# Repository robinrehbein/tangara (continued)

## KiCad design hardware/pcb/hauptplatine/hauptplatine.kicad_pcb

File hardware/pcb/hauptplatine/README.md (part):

# Hauptplatine Endgerät (Nano-Player), Rev. 3b

> **STATUS Rev. 3b (2026-10-05): Review-Korrekturen eingearbeitet, neu exportiert, ERC 0 / DRC 0 (Abgleich gegen den Schaltplan), 0 offene Verbindungen – trotzdem NICHT bestellbar:** Blocker **B4** (ESP32-S31-WROOM-1 nicht lieferbar, 21 Wochen) ist offen, ein **Opus-Zweitreview der geänderten Schaltung/Platine ist Pflicht**, und die „Offenen Punkte“ unten (u. a. H2 VDDPST_SD, H3-Rest, H5-Impedanz, H6 Molex-Footprint, H10 USB4510/1,0 mm) sind nicht erledigt. Die Fertigungsdateien in `fertigung/` sind **Entwürfe**, keine Bestelldateien.
> - Platine **41 × 97 × 1,0 mm, 4 Lagen** (F.Cu / In1 GND-Fläche / In2 Signale + GND-Fläche / B.Cu), Ecken r = 4, Gerät ca. 44 × 100 × bis 10 mm; Plattenumriss, Ausschnitte, Löcher und hohe Teile **unverändert** gegenüber Rev. 3; **für das CAD neu**: Display-Stecker J20 (Molex, Körper x ±8,35 statt ±10,6, 1,0 mm statt 2,0 mm hoch) und zwei Rückseiten-Taster SW2/SW3 (Rückwand-Löcher), siehe Tabelle „Mechanik und Übergabe an das CAD“. Antenne des WROOM-1 liegt **innerhalb** der Kante (Keepout 18,6 × 7,6 mm, alle vier Kupferlagen, Regelbereich `antenna_keepout_board`). Lagenaufbau-Referenz (PCBWay 1,0 mm, aussen/innen 1 oz, Prepreg 7628 0,1855 mm, Kern 0,43 mm) ist in der Platinendatei hinterlegt, **von PCBWay für diese Bestellung nicht bestätigt**.
> - **DRC (kicad-cli, mit Abgleich gegen den Schaltplan): 0 Verstöße, 0 unverbundene Pads, 0 Footprint-Hinweise.** ERC: 0 Meldungen. Regeln: Bahn/Abstand 0,127 mm, Via 0,45/0,2 mm, **Kupfer–Kante 0,3 mm** (PCBWay-Standard; nur die Pads von Klinke/USB-C/microSD dürfen per eigener Regel in `hauptplatine.kicad_dru` bis 0,2 mm an den Randausschnitt), Loch–Loch 0,3 mm. Abgeschaltet und begründet: `silk_over_copper`, `silk_overlap`, `silk_edge_clearance` (PCBWay schneidet Siebdruck über Pads/Kante automatisch ab), `nonmirrored_text_on_back_layer`. Referenzbezeichner sind absichtlich **nicht** im Siebdruck (PCBWay arbeitet nach CPL).
> - **Was Rev. 3b gegenüber Rev. 3 ändert (Review `docs/REVIEW-HAUPTPLATINE.md`, Abschnitt 7):** B1 PCA9306 VREF2 = EN (ein 200 k, 100 pF); B2 R57 nicht bestückt; B3 Lader SEL = GND, PROG2 fest 500 mA, R39 2,7 k (ca. 370 mA); H1 Reset-Sicherung Q21/Q22/R250 (RESET bleibt ohne 3V3 low); H3 Leistungsnetze verbreitert (VBAT und VBUS jetzt fast durchgehend ≥ 0,4 mm, SYS_POWER zu 59 %, V5_HOST zu 59 %, VBUS_SW zu 66 %, 3V3-Zuleitung und BOOST_SW nur stellenweise bzw. weiter schmal); H4 J20 = Molex 503480-30 (1,0 mm) statt Hirose FH12 (2,0 mm); H5 USB-HS-Paar ca. 72 mm gekoppelt auf F.Cu; H7 R1 DNP-Option; H8 BOOT-/EN-Taster SW2/SW3 auf der Rückseite.
> - **Wie die Änderungen entstanden (ehrlich):** Der Ausgangsstand (Rev. 3, Router Freerouting 1.9.0 plus Handnacharbeit, siehe „Neuaufbau“) wurde **nicht neu geroutet**, sondern mit einem eigenen Raster-A*-Router (`tools/rt.py`, `tools/rev3b_stage*.py`, Ablauf `tools/rev3b_make.sh`) gezielt geändert: betroffene Pads umgenetzt, Bahnen entfernt/neu gezogen, USB-Paar neu verlegt (dabei wurde ein 3V3-Abschnitt auf andere Lagen verlegt). Alles ist per DRC mit exakter Abstandsprüfung geprüft, aber **nicht** von Hand nachgeprüft; Vorschaubilder ansehen.
> - **Nicht geprüft / Risiken:** keine Hardware, keine Simulation. USB-HS: Paar gekoppelt, **Impedanz nicht bestätigt** (Aufbau- und Breitenwahl bei PCBWay, Abschnitt „USB-HS“); Analogführung (HPREFA/B, Ladungspumpe) vom Router; Footprint des **Molex 503480** (J21, J20): Nagelpads geschätzt, **Form und Y-Lage ungeprüft**; Pegel der neuen Reset-Sicherung (2N7002T Vgs(th) nur aus dem Gedächtnis); CPL-Drehungen nicht gegen PCBWay geprüft; LCSC-Nummern größtenteils nicht verifiziert (Spalte „Nummer geprueft“).
> - Die Gerber-ZIP heißt nur dann ohne „NICHT_BESTELLEN“, wenn `tools/export.py` einen sauberen DRC sieht (hier der Fall); das heißt **nicht**, dass sie bestellbar ist.

Grundlage: `docs/AUDIO.md` (Audio-Kette), `TEILE.md` (Chipliste, Ziel-Maße). KiCad 9, Schaltplan und Platine werden aus Python-Skripten erzeugt (`tools/`). Rev. 2 (37 × 86 × 0,8) ist ersetzt, weil dort die Fläche nicht reichte und das Routing scheiterte.

## Inhalt des Ordners

| Pfad | Inhalt |
|---|---|
| `hauptplatine.kicad_pro`, `.kicad_sch`, `.kicad_pcb` | KiCad-Projekt (Schaltplan A1, eine Seite) |
| `lib/` | eigene Symbole (`Hauptplatine.kicad_sym`) und Footprints (`Hauptplatine.pretty`: ESP32-S31-WROOM-1 selbst erzeugt, Klinke und USB-C aus Tangara, X2QFN, Akkupads, Befestigungsloch) |
| `fertigung/hauptplatine_gerber_bohrdaten.zip` | Gerber (4 Lagen, 1,0 mm, Maske, Paste, Silkscreen, Kontur) und Bohrdaten (Excellon, PTH/NPTH getrennt) |
| `fertigung/hauptplatine_BOM_PCBWay.csv` | Stückliste im PCBWay-Format (Designator, Menge, Hersteller, MPN, Beschreibung, Gehäuseform, LCSC/Digi-Key nur wo geprüft; DNP markiert) |
| `fertigung/hauptplatine_CPL_PCBWay.csv` | Bestückungsdatei Oberseite und Unterseite (Designator, Mid X/Y, Layer, Rotation), ohne DNP-Teile |
| `fertigung/hauptplatine_schaltplan.pdf` | Schaltplan als PDF |
| `vorschau/` | SVG/PNG der Ober- und Unterseite |
| `pruefung/erc.rpt`, `pruefung/drc.rpt` | Berichte von `kicad-cli` |
| `quellen/` | Quellen: Tangara-Netzliste (Rev. 5), Tangara-Footprints, Lizenztexte |
| `tools/` | Generatoren, Routing-Skripte (`rt.py`, `rev3b_*.py` für die Review-Korrekturen), `routing/` (Zwischenstände; `stand_vor_review_fixes.kicad_pcb` = Rev. 3 vor den Korrekturen) |
| `LICENSE` | CERN-OHL-S-2.0 |

## Blockschaltbild

```
USB-C (J6, GCT USB4510) --CC1/CC2--> TUSB320LAI (U12, DRP) --ID/INT--> S31
   | D+/D- (R102/R103)                       |
   |                                          v HOST_EN
   +--VBUS--> PE1605 (U5) --> Q1 --> MCP73871 (U10, Power-Path) <--> LiPo 303450 (BT1-Pads, NTC)
   |                                |  SYS_POWER                         |
   +<-- TPS2553 (U21) <-- TPS61023 (U20, 5,1 V) <-- SYS_POWER           MAX17048 (U22, I2C 0x36)
                                    |
              SW1 -> LDO_EN / S31 haelt SYS_PWR_EN (Power-Latch)
                                    v
                      TLV75733 (U4, 3V3, 1 A) ----------------------------------------+
                                    |                                                    |
 ESP32-S31-WROOM-1-N16R16V (U15)  3V3                                                    |
  WLAN 6, BT 5.4 Classic + LE Audio, USB-HS-OTG, 16 MB Flash + 16 MB PSRAM               |
    |QSPI+I2C+INT      |I2S (Slave)         |SDMMC 4 Bit        |I2C                      |
    v                  v                    v                   v                         |
 AMOLED 2,06" (J20)   Pegelwandler U31-U33  microSD (J4)        Klickrad (J21, Molex 503480-0600)     |
 CO5300 410x502       1,8 V <-> 3,3 V       (TPS22948 U16)      AT42QT2120 + DRV2605L     |
                           |                                                              |
                  CS43131 (U17), I2S-Master, Quarz 22,5792 MHz (X1) <-- 1,8-V-LDO (U34) <-+
                  VP aus SYS_POWER, I2C ueber PCA9306 (U30)
                           |HPOUTA/B + HPREFA/B + HP_DETECT
                           v
                  Klinke SJ-43504-SMT-TR (J1, Randausschnitt) + ESD D5V0L2B3T-7 (U3)

 Audio-Weg A (Kabel, Hi-Res): S31 --I2S--> CS43131 (24 Bit/192 kHz, Class-H-Verstaerker) --> Klinke
 Audio-Weg B (digital):       S31 --USB-HS-OTG (Host, UAC2)--> USB-C --> externer USB-DAC (TUSB320 stellt "Quelle" ein, TPS61023 + TPS2553 liefern 5 V)
 Weg C (drahtlos):            S31 --Bluetooth--> Kopfhoerer (A2DP, in der Regel SBC; LC3 nur mit LE Audio auf beiden Seiten)
```

## Festgelegte Chips

| Funktion | Chip | Bezeichner | Herkunft |
|---|---|---|---|
| MCU | ESP32-S31-**WROOM-1**-N16R16V (18 × 25,5 × 3,1 mm, 16 MB Flash, 16 MB PSRAM) | U15 | neu (WROOM-3 nicht nötig, siehe GPIO-Prüfung) |
| DAC + Kopfhörerverstärker | Cirrus **CS43131**-CNZR (QFN-40), Quarz 22,5792 MHz, DAC = I²S-Master | U17, X1 | neu (`docs/AUDIO.md`; Tangara: WM8523 + INA1620 + TPS65133) |
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
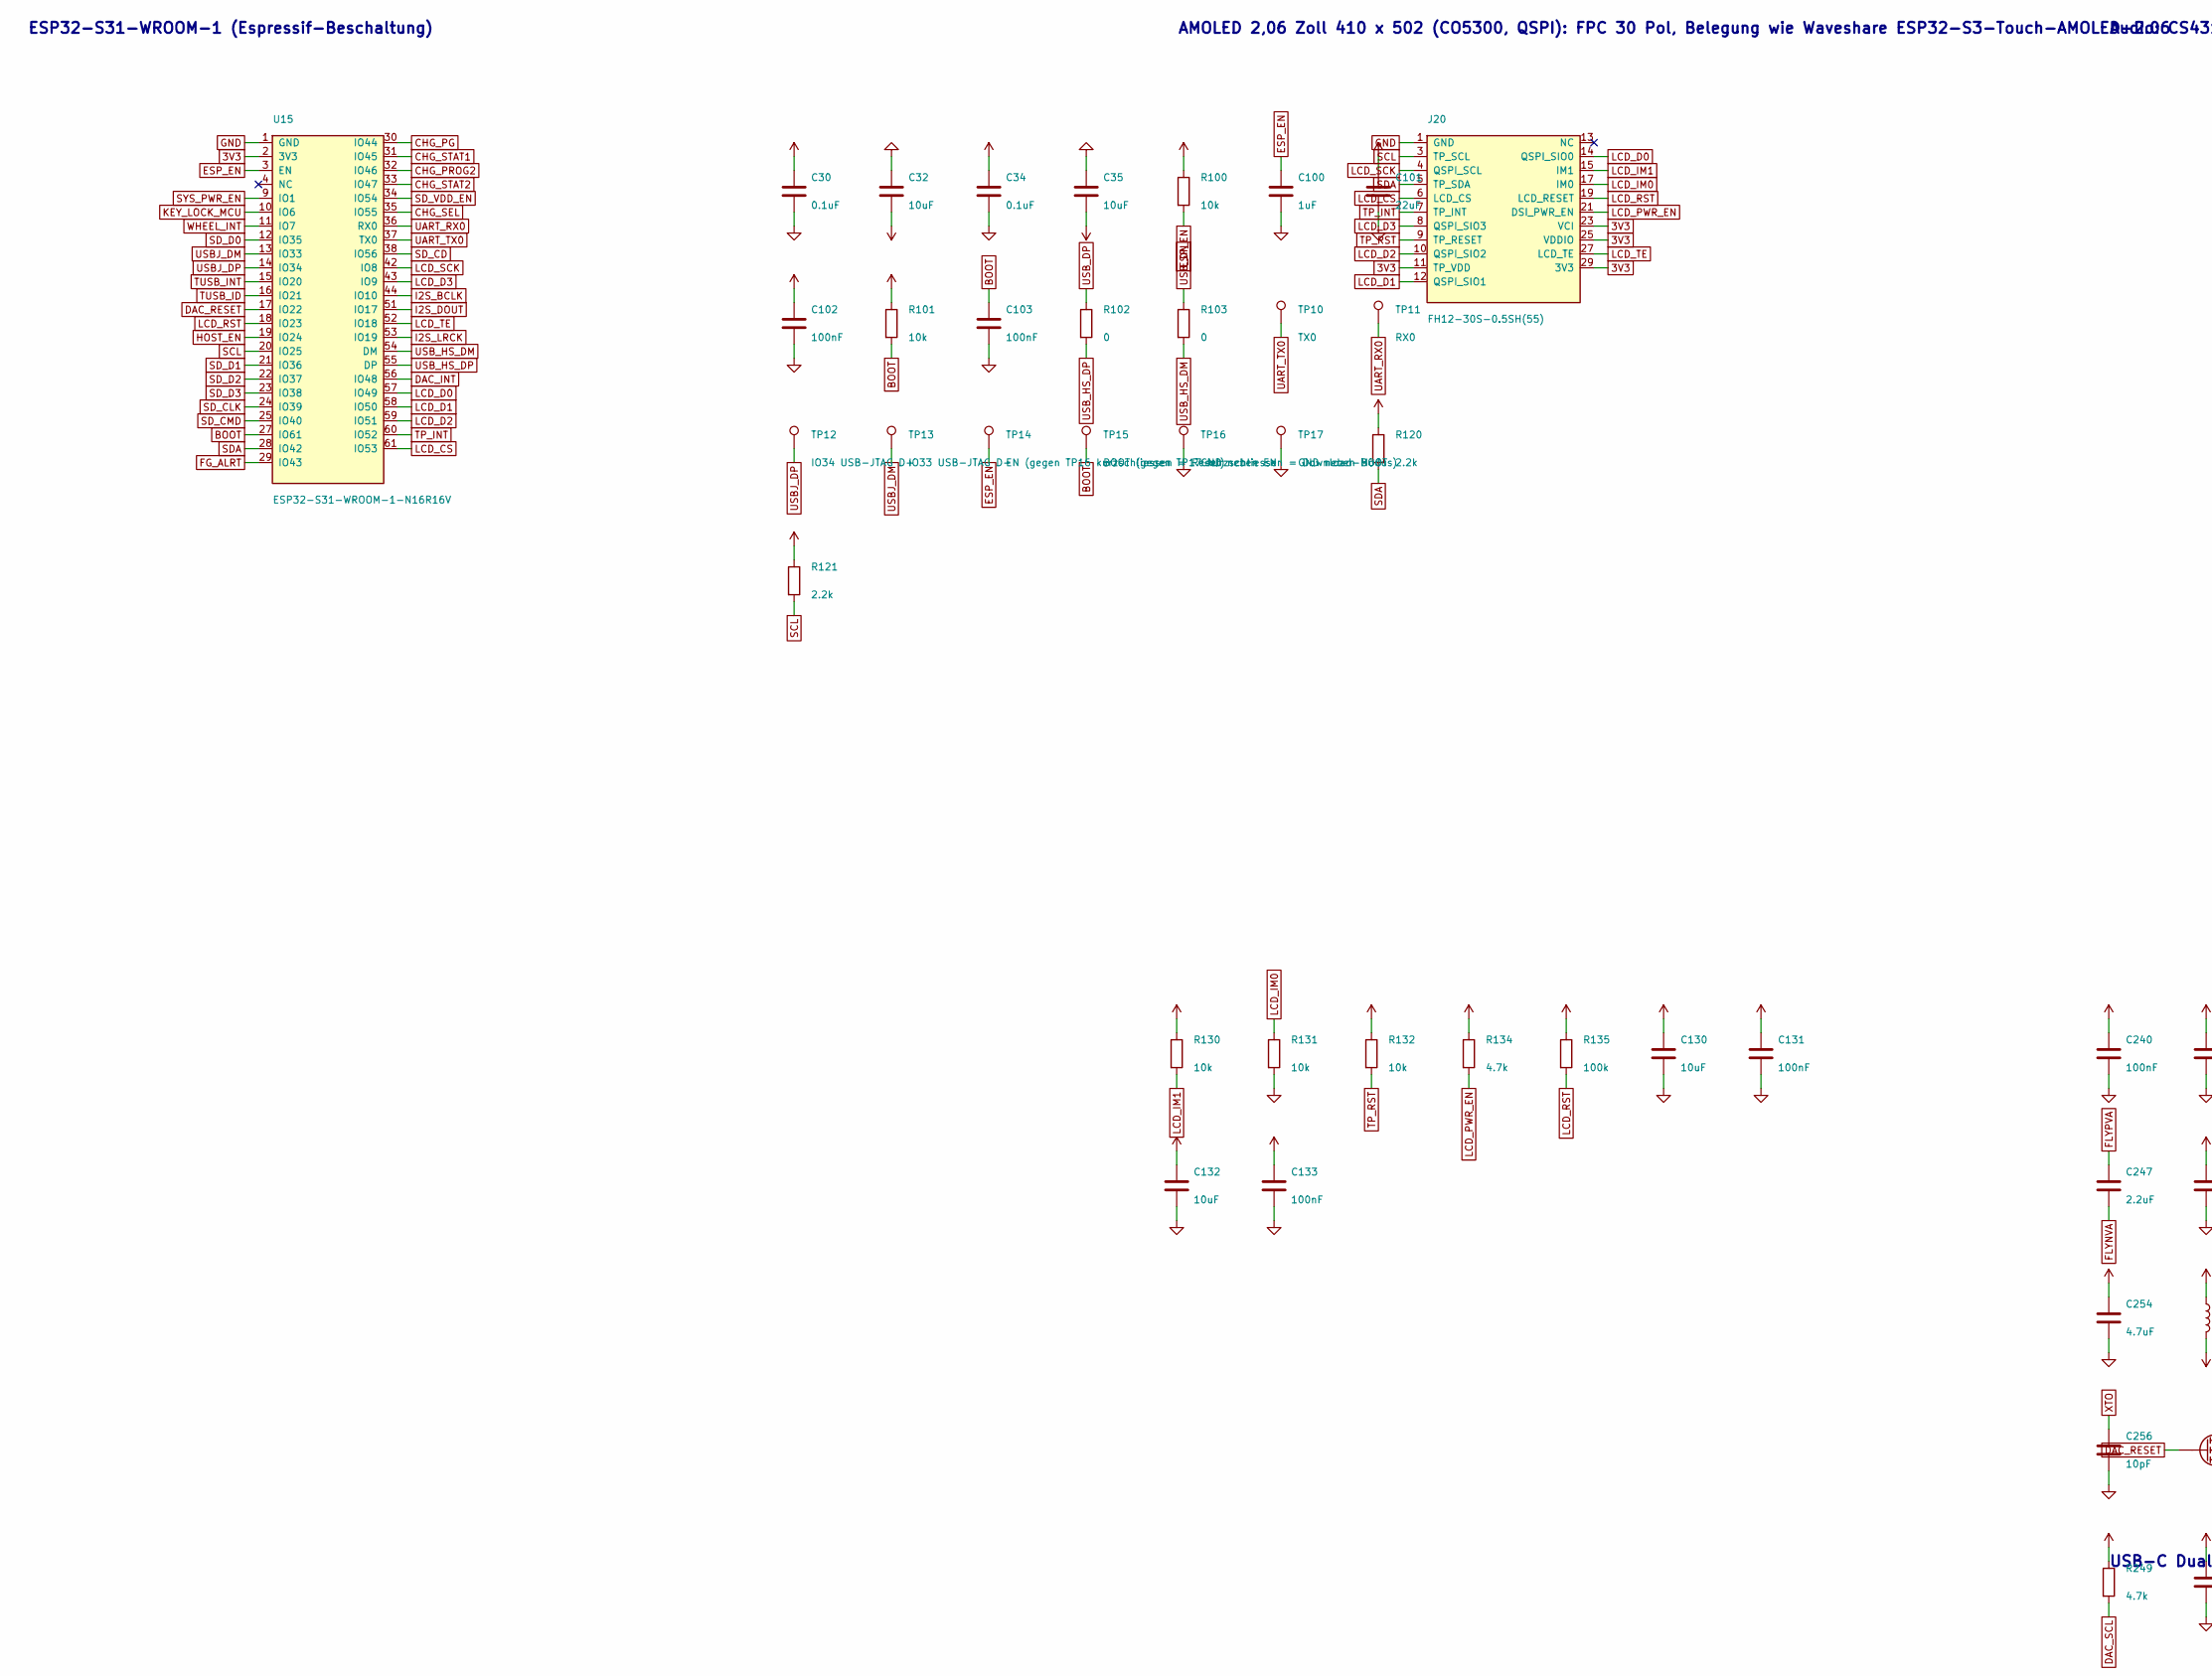
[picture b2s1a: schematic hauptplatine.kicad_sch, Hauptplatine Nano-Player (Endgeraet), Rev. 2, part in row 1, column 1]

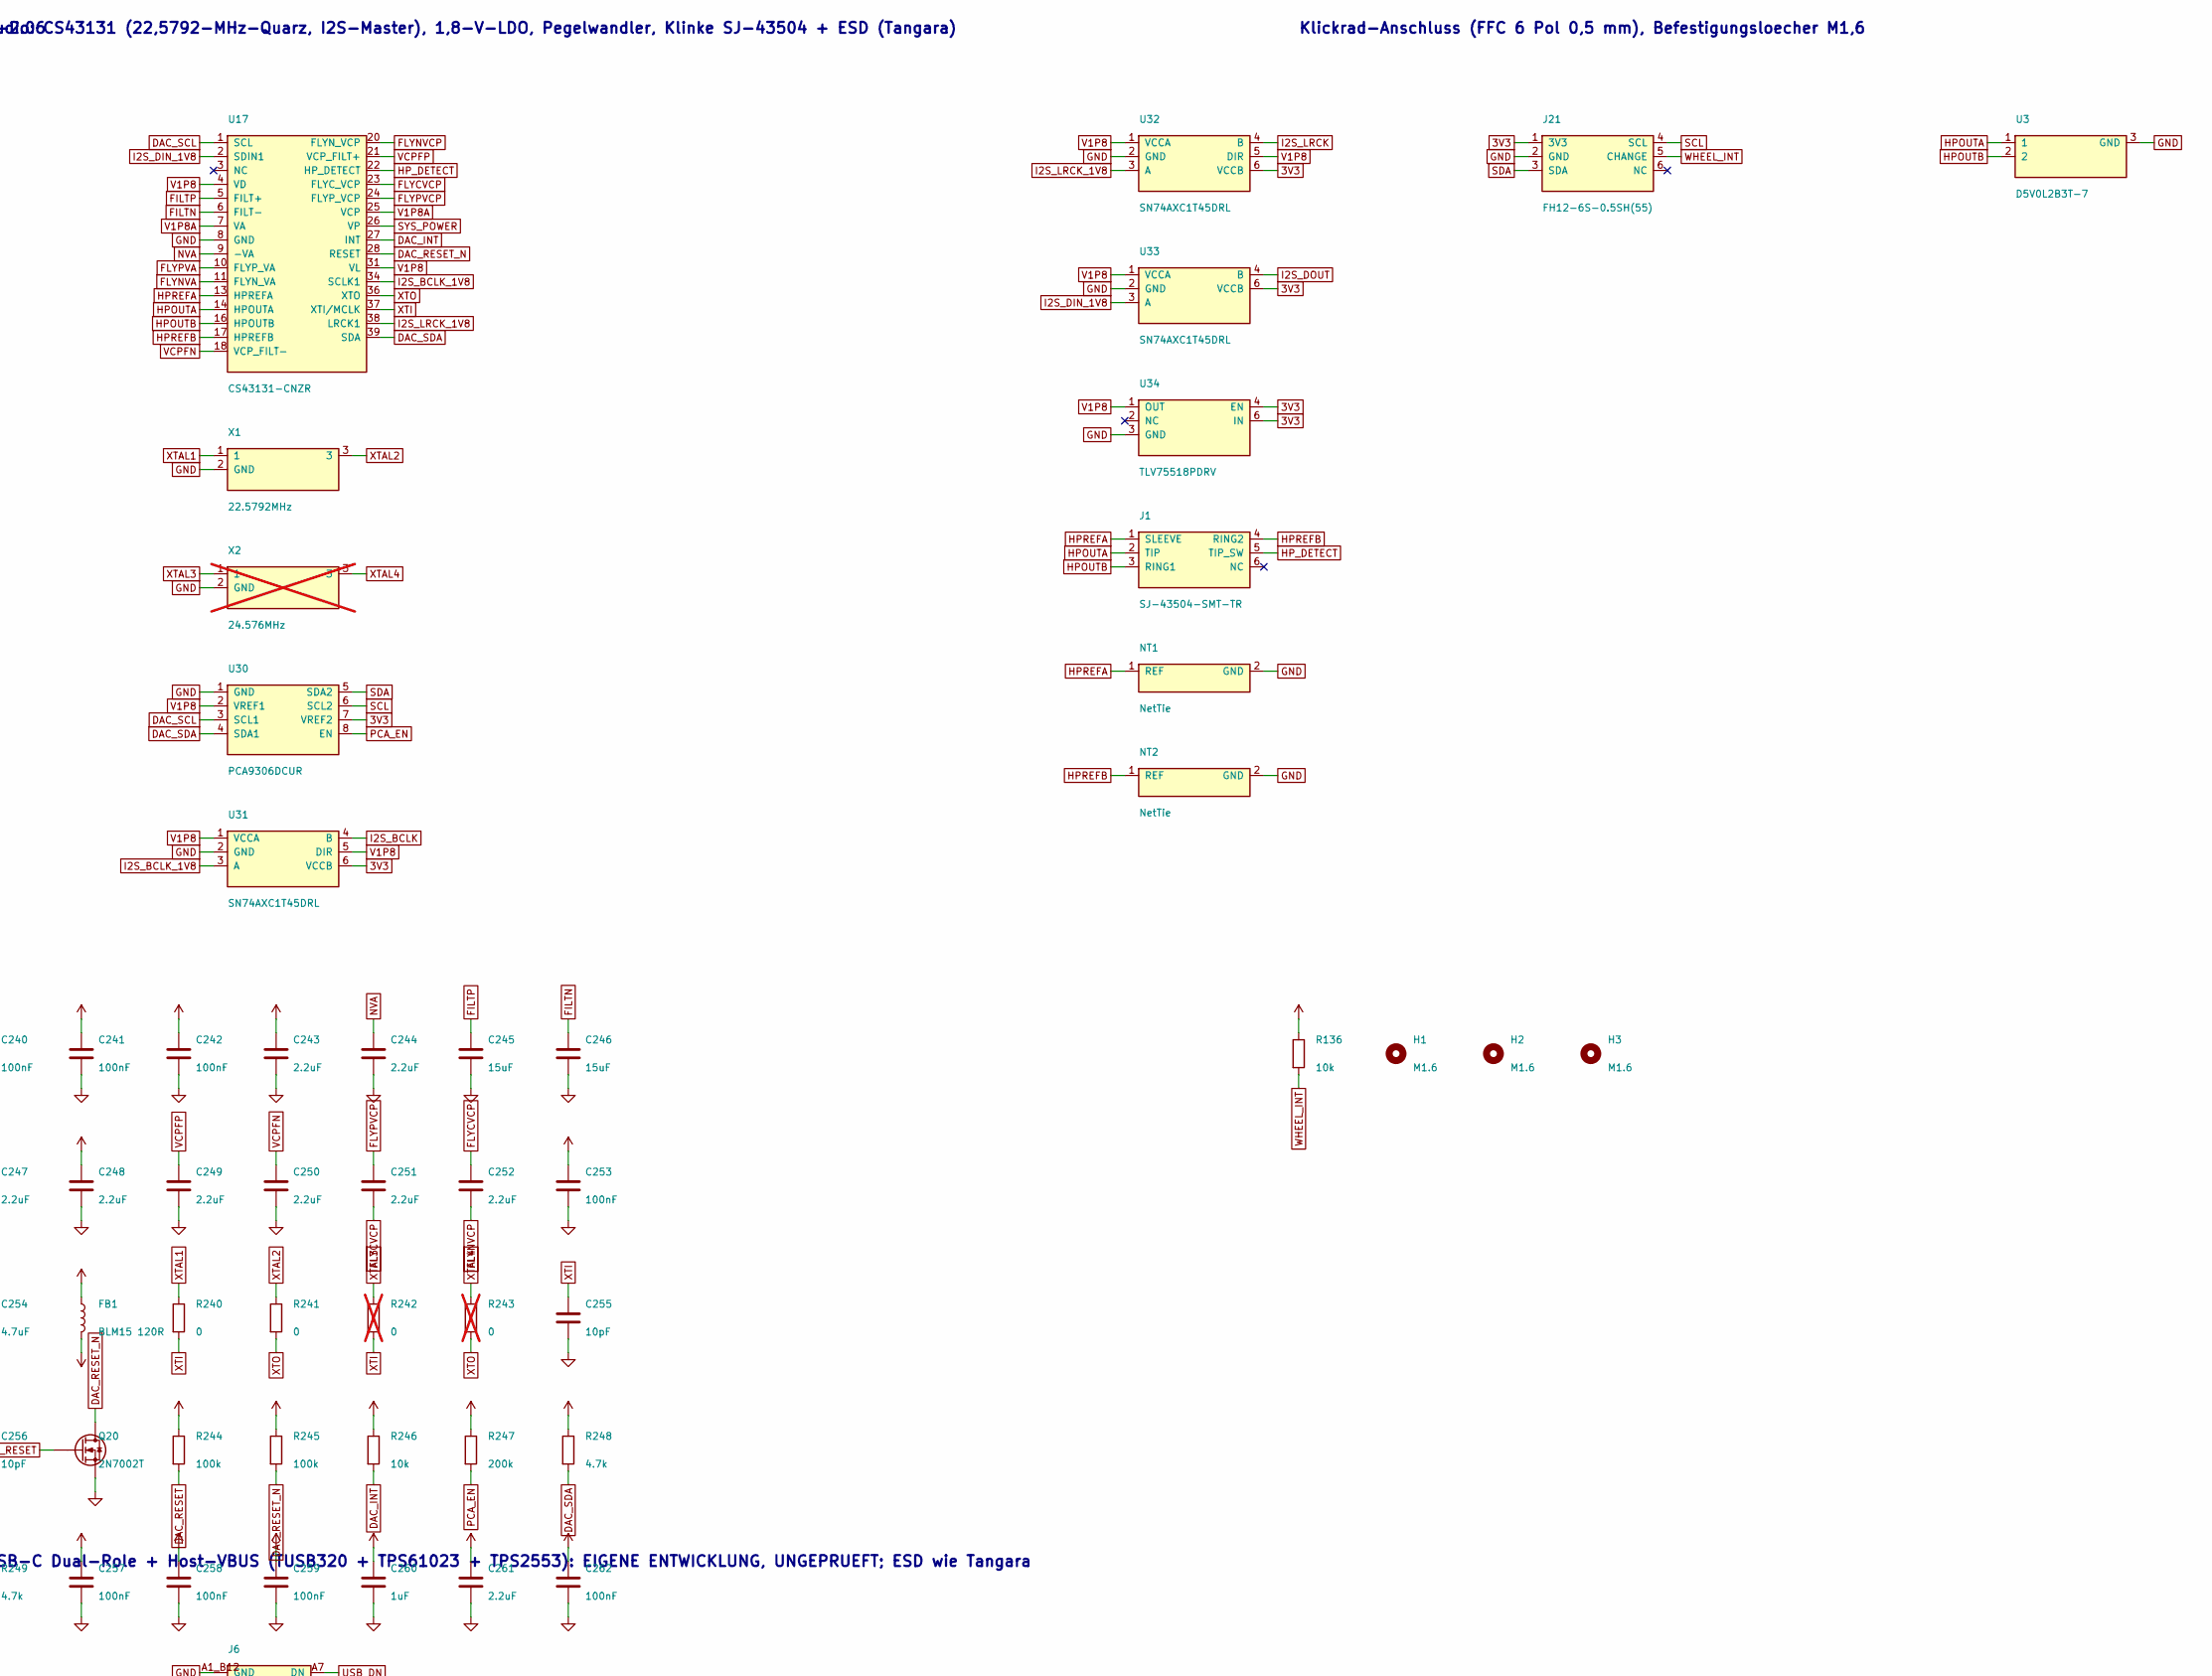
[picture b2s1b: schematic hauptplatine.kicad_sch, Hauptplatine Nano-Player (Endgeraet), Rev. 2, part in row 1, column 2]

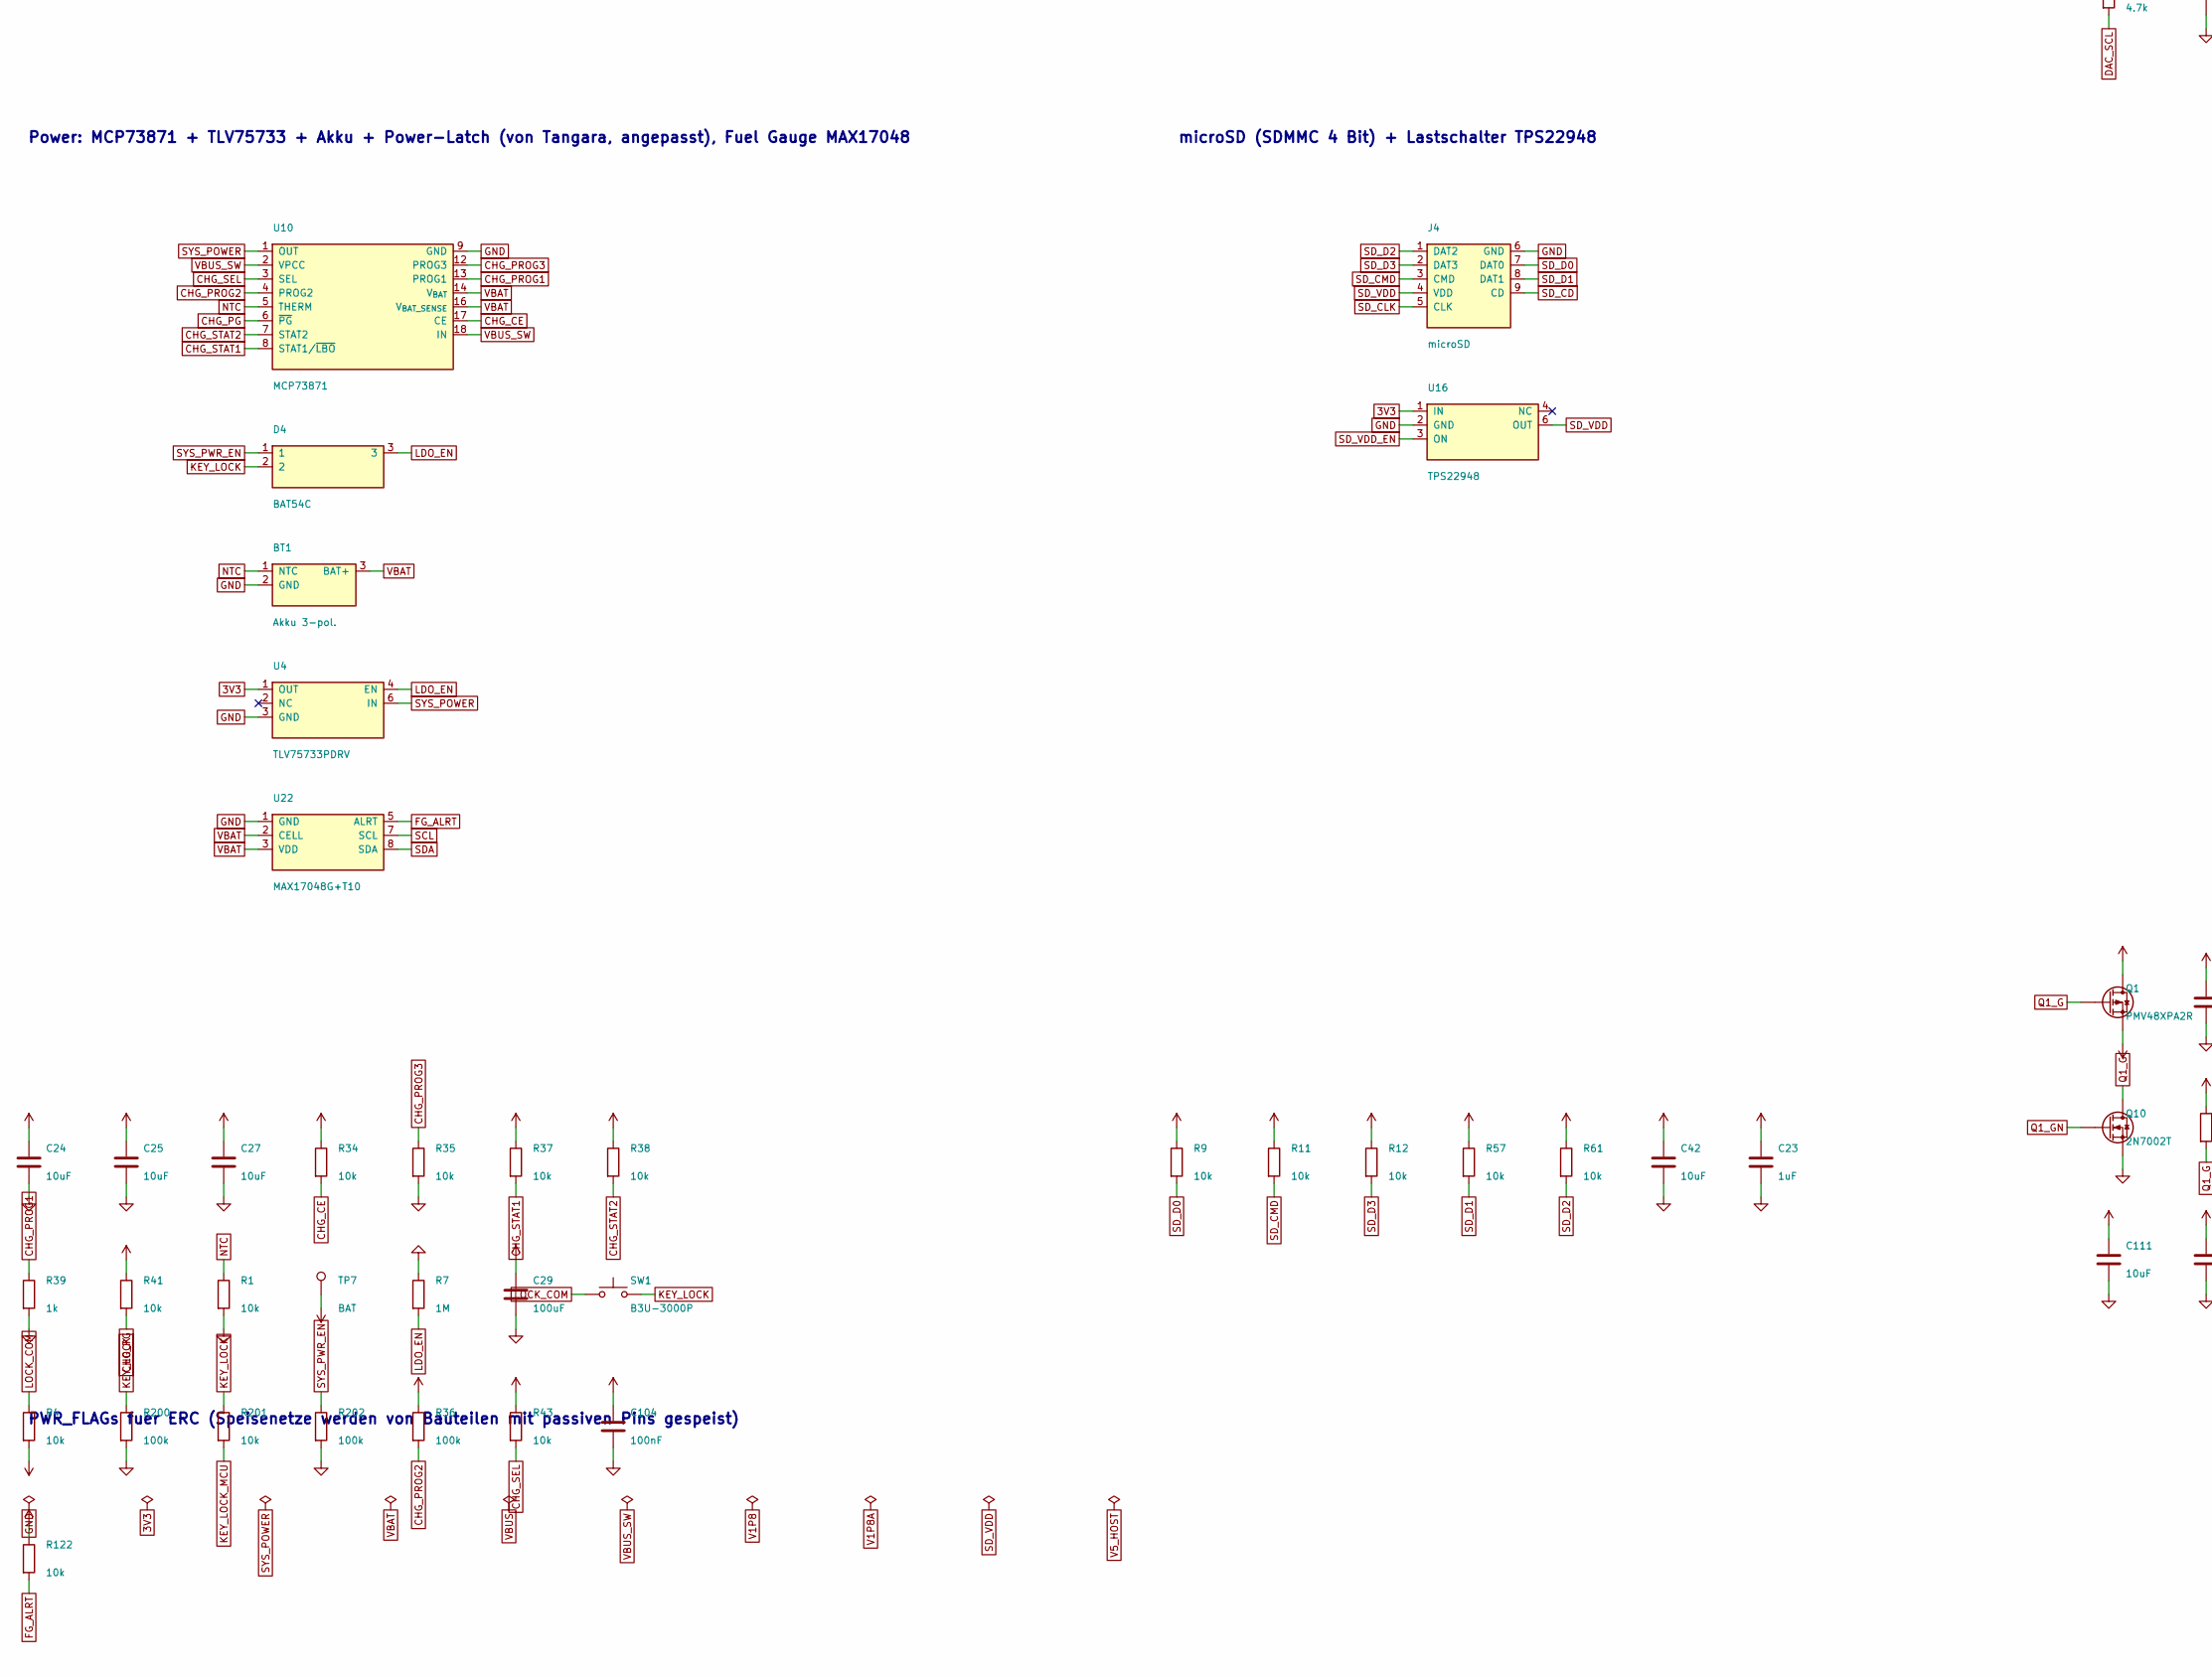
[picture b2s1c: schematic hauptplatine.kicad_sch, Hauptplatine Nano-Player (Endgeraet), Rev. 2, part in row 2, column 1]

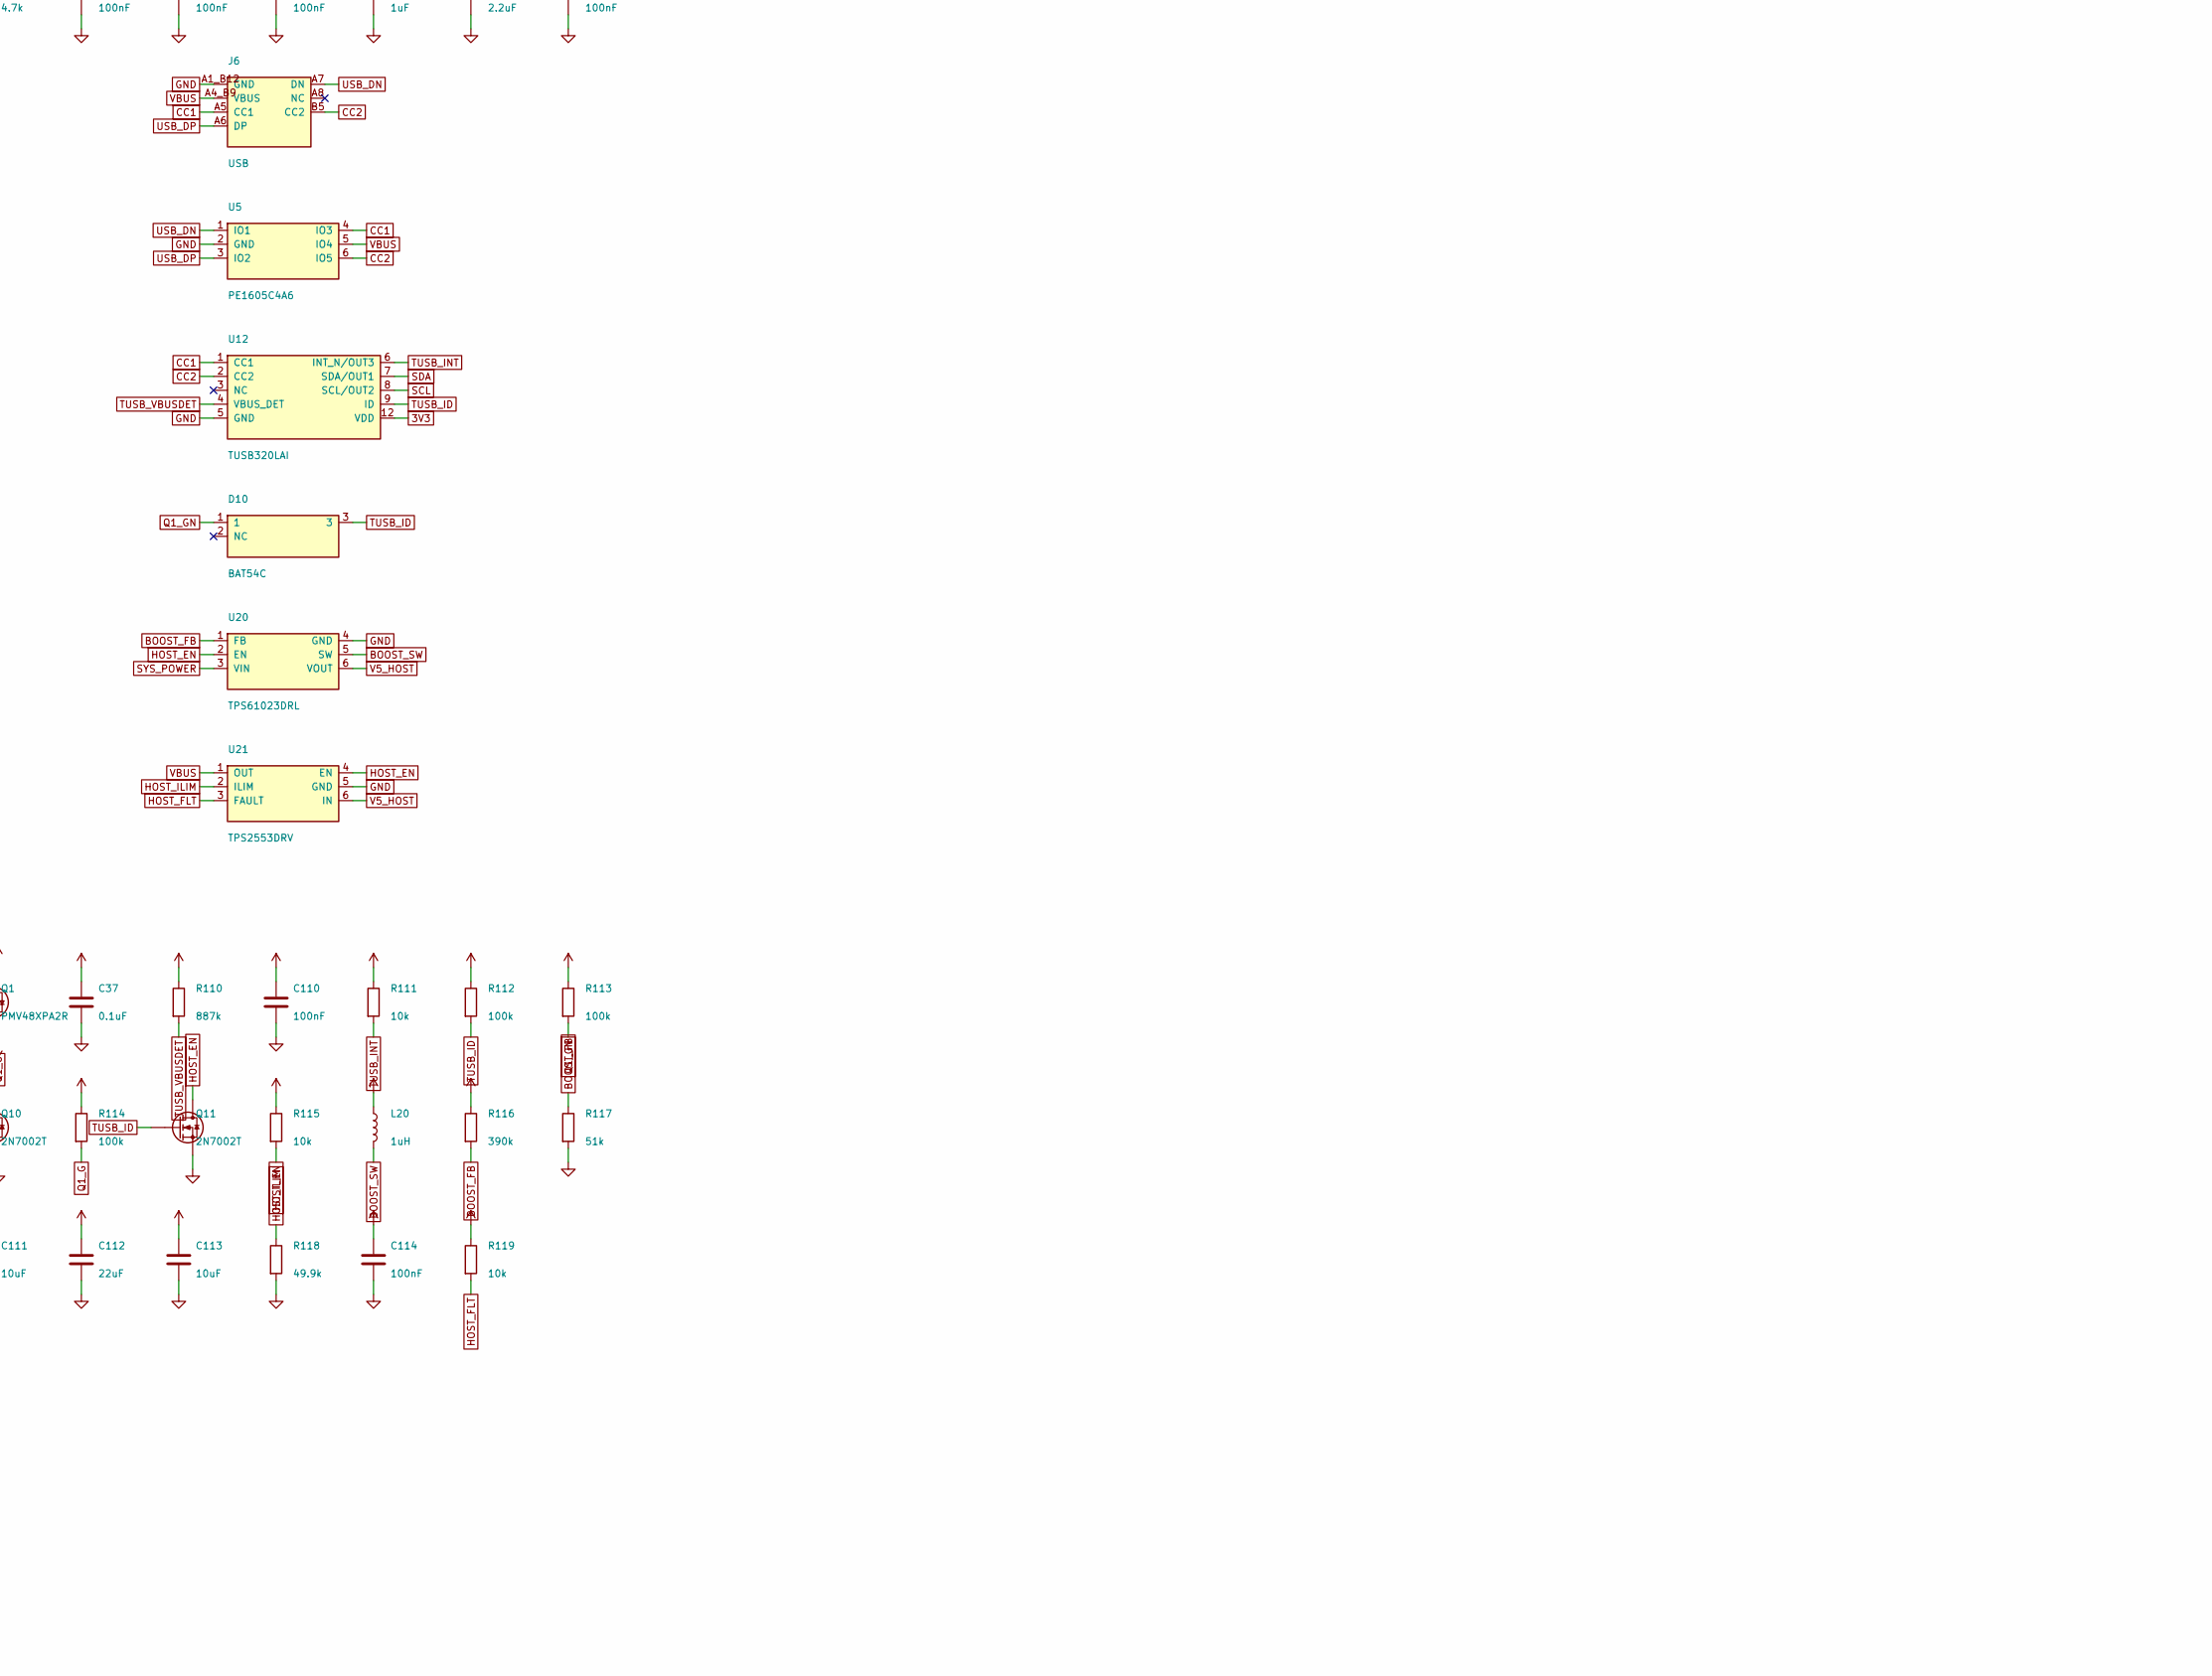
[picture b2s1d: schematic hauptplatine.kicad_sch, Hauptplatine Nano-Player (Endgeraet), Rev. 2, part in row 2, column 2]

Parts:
BT1: Akku 3-pol.; BATT_PADS_3
C23: 1uF; C_0603_1608Metric; MPN GRM188R61A105KA61D
C24, C25, C27, C32, C35, C42, C111, C113: 10uF; C_0603_1608Metric; MPN GRM188R61A106KE69
C29: 100uF; C_1210_3225Metric; MPN GRM32EC70J107ME15K
C30, C34, C37: 0.1uF; C_0603_1608Metric; MPN GCM188R71C104KA37J
C100, C260: 1uF; C_0402_1005Metric; MPN CL05A105KA5NQNC; LCSC C52923
C101, C112: 22uF; C_0603_1608Metric; MPN GRM188R60J226MEA0
C102, C103, C104, C110, C114, C131, C133, C240, C241, C242, C253, C257, C258, C259, C262: 100nF; C_0402_1005Metric; MPN CL05B104KO5NNNC; LCSC C1525
C130, C132: 10uF; C_0402_1005Metric; MPN GRM155R60J106ME05D
C243, C244, C247, C248, C249, C250, C251, C252, C261: 2.2uF; C_0402_1005Metric; MPN GRM155R60J225ME15D
C245, C246: 15uF; C_0603_1608Metric; MPN (15 uF X5R >= 6,3 V 0603, Typ nach Verf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
C254: 4.7uF; C_0603_1608Metric; MPN GRM188R60J475KE19D
C255, C256: 10pF; C_0402_1005Metric; MPN GRM1555C1H100JA01D
D4, D10: BAT54C; SOT-23; MPN BAT54C
FB1: BLM15 120R; L_0402_1005Metric; MPN BLM15AG121SN1D
H1, H2, H3: M1.6; MountingHole_1.8mm
J1: SJ-43504-SMT-TR; CUI_SJ-43504-SMT-TR; MPN SJ-43504-SMT-TR
J4: microSD; microSD_HC_Molex_104031-0811; MPN 104031-0811; DigiKey WM6357DKR-ND
J6: USB; GCT_USB4510-03-1-A_REVA; MPN USB4510-03-1-A
J20: FH12-30S-0.5SH(55); Hirose_FH12-30S-0.5SH_1x30-1MP_P0.50mm_Horizontal; MPN FH12-30S-0.5SH(55)
J21: FH12-6S-0.5SH(55); Hirose_FH12-6S-0.5SH_1x06-1MP_P0.50mm_Horizontal; MPN FH12-6S-0.5SH(55)
L20: 1uH; L_0805_2012Metric; MPN DFE201610E-1R0M=P2
NT1, NT2: NetTie; NetTie-2_SMD_Pad0.5mm
Q1: PMV48XPA2R; TSOT-23; MPN PMV48XPA2R
Q10, Q11, Q20: 2N7002T; SOT-523; MPN 2N7002T-7-F
R1: 10k; R_0603_1608Metric; MPN 0.1W 5%
R4, R9, R11, R12, R34, R35, R37, R38, R41, R43, R57, R61, R201: 10k; R_0603_1608Metric; MPN AC0603JR-0710KL
R7: 1M; R_0603_1608Metric; MPN AC0603FR-131ML
R36, R200, R202: 100k; R_0603_1608Metric; MPN AC0603FR-07100KL
R39: 1k; R_0603_1608Metric; MPN RC0603DR-071KL
R100, R101, R111, R115, R119, R122, R130, R131, R132, R136, R246: 10k; R_0402_1005Metric; MPN 0402WGF1002TCE; LCSC C25744
R102, R103, R240, R241: 0; R_0402_1005Metric; MPN 0402WGF0000TCE; LCSC C17168
R110: 887k; R_0402_1005Metric
R112, R113, R114, R135, R244, R245: 100k; R_0402_1005Metric; MPN 0402WGF1003TCE; LCSC C25741
R116: 390k; R_0402_1005Metric
R117: 51k; R_0402_1005Metric
R118: 49.9k; R_0402_1005Metric
R120, R121: 2.2k; R_0402_1005Metric; MPN 0402WGF2201TCE; LCSC C25879
R134, R248, R249: 4.7k; R_0402_1005Metric; MPN 0402WGF4701TCE; LCSC C25900
R242, R243: 0; R_0402_1005Metric; MPN 0402WGF0000TCE; LCSC C17168; not fitted
R247: 200k; R_0402_1005Metric
SW1: B3U-3000P; SW_SPST_B3U-3000P; MPN B3U-3000P; LCSC C963349
TP7: BAT; TestPoint_Pad_D1.0mm
TP10: TX0; TestPoint_Pad_D1.0mm
TP11: RX0; TestPoint_Pad_D1.0mm
TP12: IO34 USB-JTAG D+; TestPoint_Pad_D1.0mm
TP13: IO33 USB-JTAG D-; TestPoint_Pad_D1.0mm
TP14: EN (gegen TP16 kurzschliessen = Reset); TestPoint_Pad_D1.0mm
TP15: BOOT (gegen TP17 kurzschliessen = Download-Modus); TestPoint_Pad_D1.0mm
TP16: GND neben EN; TestPoint_Pad_D1.0mm
TP17: GND neben BOOT; TestPoint_Pad_D1.0mm
U3: D5V0L2B3T-7; SOT-523; MPN D5V0L2B3T-7
U4: TLV75733PDRV; WSON-6-1EP_2x2mm_P0.65mm_EP1x1.6mm; MPN TLV75733PDRVR
U5: PE1605C4A6; SOT-23-6; MPN PE1605C4A6
U10: MCP73871; QFN-20-1EP_4x4mm_P0.5mm_EP2.5x2.5mm; MPN MCP73871-2CCI/ML
U12: TUSB320LAI; X2QFN-12-RWB; MPN TUSB320LAIRWBR; LCSC C132554
U15: ESP32-S31-WROOM-1-N16R16V; ESP32-S31-WROOM-1; MPN ESP32-S31-WROOM-1-N16R16V
U16: TPS22948; SOT65P210X110-6N; MPN TPS22948DCKR
U17: CS43131-CNZR; QFN-40-1EP_5x5mm_P0.4mm_EP3.6x3.6mm; MPN CS43131-CNZR; DigiKey 598-CS43131-CNZRCT-ND
U20: TPS61023DRL; SOT-563; MPN TPS61023DRLR; LCSC C919459
U21: TPS2553DRV; WSON-6-1EP_2x2mm_P0.65mm_EP1x1.6mm; MPN TPS2553DRVR
U22: MAX17048G+T10; TDFN-8-1EP_2x2mm_P0.5mm_EP0.8x1.2mm; MPN MAX17048G+T10; LCSC C2682616
U30: PCA9306DCUR; VSSOP-8_2.3x2mm_P0.5mm; MPN PCA9306DCUR
U31, U32, U33: SN74AXC1T45DRL; SOT-563; MPN SN74AXC1T45DRLR
U34: TLV75518PDRV; WSON-6-1EP_2x2mm_P0.65mm_EP1x1.6mm; MPN TLV75518PDRVR
X1: 22.5792MHz; Crystal_SMD_2016-4Pin_2.0x1.6mm; MPN NX2016SA 22.5792M EXS00A-CS09116
X2: 24.576MHz; Crystal_SMD_2016-4Pin_2.0x1.6mm; MPN NX2016SA 24.576M EXS00A-CS09117; not fitted

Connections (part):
3V3: C23.1, C29.1, C30.1, C32.2, C34.1, C35.2, C101.1, C102.1, C110.1, C130.1, C131.1, C132.1, C133.1, C257.1, C258.1, C259.1, C260.1, J20.11 (TP_VDD), J20.23 (VCI), J20.25 (VDDIO), J20.29 (3V3), J20.30 (3V3), J21.1 (3V3), R36.1, R37.1, R38.1, R41.1, R43.1, R100.1, R101.1, R111.1, R112.1, R115.1, R119.1, R120.1, R121.1, R122.1, R130.1, R132.1, R134.1, R135.1, R136.1, R244.1, R246.1, R247.1, U4.1 (OUT), U12.12 (VDD), U15.2 (3V3), U16.1 (IN), U30.7 (VREF2), U31.6 (VCCB), U32.6 (VCCB), U33.6 (VCCB), U34.4 (EN), U34.6 (IN)
BOOST_FB: R116.2, R117.1, U20.1 (FB)
BOOST_SW: L20.2, U20.5 (SW)
BOOT: C103.1, R101.2, TP15.1, U15.27 (IO61)
CC1: J6.A5 (CC1), U5.4 (IO3), U12.1 (CC1)
CC2: J6.B5 (CC2), U5.6 (IO5), U12.2 (CC2)
CHG_CE: R34.2, U10.17 (CE)
CHG_PG: R41.2, U10.6 (~PG), U15.30 (IO44)
CHG_PROG1: R39.1, U10.13 (PROG1)
CHG_PROG2: R36.2, U10.4 (PROG2), U15.32 (IO46)
CHG_PROG3: R35.1, U10.12 (PROG3)
CHG_SEL: R43.2, U10.3 (SEL), U15.35 (IO55)
CHG_STAT1: R37.2, U10.8 (STAT1/~LBO), U15.31 (IO45)
CHG_STAT2: R38.2, U10.7 (STAT2), U15.33 (IO47)
DAC_INT: R246.2, U15.56 (IO48), U17.27 (INT)
DAC_RESET: Q20.1 (G), R244.2, U15.17 (IO22)
DAC_RESET_N: Q20.3 (D), R245.2, U17.28 (RESET)
DAC_SCL: R249.2, U17.1 (SCL), U30.3 (SCL1)
DAC_SDA: R248.2, U17.39 (SDA), U30.4 (SDA1)
ESP_EN: C100.1, R100.2, TP14.1, U15.3 (EN)
FG_ALRT: R122.2, U15.29 (IO43), U22.5 (ALRT)
FILTN: C246.1, U17.6 (FILT-)
FILTP: C245.1, U17.5 (FILT+)
FLYCVCP: C251.2, C252.1, U17.23 (FLYC_VCP)
FLYNVA: C247.2, U17.11 (FLYN_VA)
FLYNVCP: C252.2, U17.20 (FLYN_VCP)
FLYPVA: C247.1, U17.10 (FLYP_VA)
FLYPVCP: C251.1, U17.24 (FLYP_VCP)
GND: BT1.2 (GND), C23.2, C24.2, C25.2, C27.2, C29.2, C30.2, C32.1, C34.2, C35.1, C37.2, C42.2, C100.2, C101.2, C102.2, C103.2, C104.2, C110.2, C111.2, C112.2, C113.2, C114.2, C130.2, C131.2, C132.2, C133.2, C240.2, C241.2, C242.2, C243.2, C244.2, C245.2, C246.2, C248.2, C249.2, C250.2, C253.2, C254.2, C255.2, C256.2, C257.2, C258.2, C259.2, C260.2, C261.2, C262.2, J4.6 (GND), J4.10 (GND), J4.11 (GND), J6.A1_B12 (GND), J6.B1_A12 (GND), J6.S1 (GND), J6.S2 (GND), J6.S3 (GND), J6.S4 (GND), J20.1 (GND), J20.2 (GND), J20.16 (GND), J20.18 (GND), J20.20 (GND), J20.22 (GND), J20.24 (GND), J20.26 (GND), J20.28 (GND), J20.MP (GND), J21.2 (GND), J21.MP (GND), NT1.2 (GND), NT2.2 (GND), Q10.2 (S), Q11.2 (S), Q20.2 (S), R1.2, R7.1, R35.2, R39.2, R117.2, R118.2, R131.2, R200.2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
HOST_EN: Q11.3 (D), R115.2, U15.19 (IO24), U20.2 (EN), U21.4 (EN)
HOST_FLT: R119.2, U21.3 (FAULT)
HOST_ILIM: R118.1, U21.2 (ILIM)
HPOUTA: J1.2 (TIP), U3.1, U17.14 (HPOUTA)
HPOUTB: J1.3 (RING1), U3.2, U17.16 (HPOUTB)
HPREFA: J1.1 (SLEEVE), NT1.1 (REF), U17.13 (HPREFA)
HPREFB: J1.4 (RING2), NT2.1 (REF), U17.17 (HPREFB)
HP_DETECT: J1.5 (TIP_SW), U17.22 (HP_DETECT)
I2S_BCLK: U15.44 (IO10), U31.4 (B)
I2S_BCLK_1V8: U17.34 (SCLK1), U31.3 (A)
I2S_DIN_1V8: U17.2 (SDIN1), U33.3 (A)
I2S_DOUT: U15.51 (IO17), U33.4 (B)
I2S_LRCK: U15.53 (IO19), U32.4 (B)
I2S_LRCK_1V8: U17.38 (LRCK1), U32.3 (A)
KEY_LOCK: D4.2, R200.1, R201.1, SW1.2
KEY_LOCK_MCU: R201.2, U15.10 (IO6)
LCD_CS: J20.6 (LCD_CS), U15.61 (IO53)
LCD_D0: J20.14 (QSPI_SIO0), U15.57 (IO49)
LCD_D1: J20.12 (QSPI_SIO1), U15.58 (IO50)
LCD_D2: J20.10 (QSPI_SIO2), U15.59 (IO51)
LCD_D3: J20.8 (QSPI_SIO3), U15.43 (IO9)
LCD_IM0: J20.17 (IM0), R131.1
LCD_IM1: J20.15 (IM1), R130.2
LCD_PWR_EN: J20.21 (DSI_PWR_EN), R134.2
LCD_RST: J20.19 (LCD_RESET), R135.2, U15.18 (IO23)
LCD_SCK: J20.4 (QSPI_SCL), U15.42 (IO8)
LCD_TE: J20.27 (LCD_TE), U15.52 (IO18)
LDO_EN: D4.3, R7.2, U4.4 (EN)
LOCK_COM: R4.1, SW1.1
NTC: BT1.1 (NTC), R1.1, U10.5 (THERM)
NVA: C244.1, U17.9 (-VA)
PCA_EN: R247.2, U30.8 (EN)
Q1_G: Q1.1 (G), Q10.3 (D), R114.2
Q1_GN: D10.1, Q10.1 (G), R113.2
SCL: J20.3 (TP_SCL), J21.4 (SCL), R121.2, U12.8 (SCL/OUT2), U15.20 (IO25), U22.7 (SCL), U30.6 (SCL2)
SDA: J20.5 (TP_SDA), J21.3 (SDA), R120.2, U12.7 (SDA/OUT1), U15.28 (IO42), U22.8 (SDA), U30.5 (SDA2)
SD_CD: J4.9 (CD), U15.38 (IO56)
SD_CLK: J4.5 (CLK), U15.24 (IO39)
SD_CMD: J4.3 (CMD), R11.2, U15.25 (IO40)
SD_D0: J4.7 (DAT0), R9.2, U15.12 (IO35)
SD_D1: J4.8 (DAT1), R57.2, U15.21 (IO36)
SD_D2: J4.1 (DAT2), R61.2, U15.22 (IO37)
SD_D3: J4.2 (DAT3), R12.2, U15.23 (IO38)
SD_VDD: C42.1, J4.4 (VDD), R9.1, R11.1, R12.1, R57.1, R61.1, U16.6 (OUT)
SD_VDD_EN: U15.34 (IO54), U16.3 (ON)
SYS_POWER: C24.1, C111.1, C253.1, C254.1, L20.1, R4.2, R34.1, R245.1, U4.6 (IN), U10.1 (OUT), U10.20 (OUT), U17.26 (VP), U20.3 (VIN)
SYS_PWR_EN: D4.1, R202.1, U15.9 (IO1)
TP_INT: J20.7 (TP_INT), U15.60 (IO52)
TP_RST: J20.9 (TP_RESET), R132.2
TUSB_ID: D10.3, Q11.1 (G), R112.2, U12.9 (ID), U15.16 (IO21)
TUSB_INT: R111.2, U12.6 (INT_N/OUT3), U15.15 (IO20)
TUSB_VBUSDET: R110.2, U12.4 (VBUS_DET)
UART_RX0: TP11.1, U15.36 (RX0)
UART_TX0: TP10.1, U15.37 (TX0)
USBJ_DM: TP13.1, U15.13 (IO33)
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
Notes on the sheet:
ESP32-S31-WROOM-1 (Espressif-Beschaltung)
AMOLED 2,06 Zoll 410 x 502 (CO5300, QSPI): FPC 30 Pol, Belegung wie Waveshare ESP32-S3-Touch-AMOLED-2.06
Audio: CS43131 (22,5792-MHz-Quarz, I2S-Master), 1,8-V-LDO, Pegelwandler, Klinke SJ-43504 + ESD (Tangara)
Power: MCP73871 + TLV75733 + Akku + Power-Latch (von Tangara, angepasst), Fuel Gauge MAX17048
USB-C Dual-Role + Host-VBUS (TUSB320 + TPS61023 + TPS2553): EIGENE ENTWICKLUNG, UNGEPRUEFT; ESD wie Tangara
microSD (SDMMC 4 Bit) + Lastschalter TPS22948
Klickrad-Anschluss (FFC 6 Pol 0,5 mm), Befestigungsloecher M1,6
PWR_FLAGs fuer ERC (Speisenetze werden von Bauteilen mit passiven Pins gespeist)
